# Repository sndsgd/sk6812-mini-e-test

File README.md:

# `sk6812-mini-e-test`

I've successfully used SK6812-MINI-E LEDs in several projects recently, and I'm considering using _lots_ of them in the near future. I'll be using this little board to verify performance and power requirements before scaling to thousands of LEDs.

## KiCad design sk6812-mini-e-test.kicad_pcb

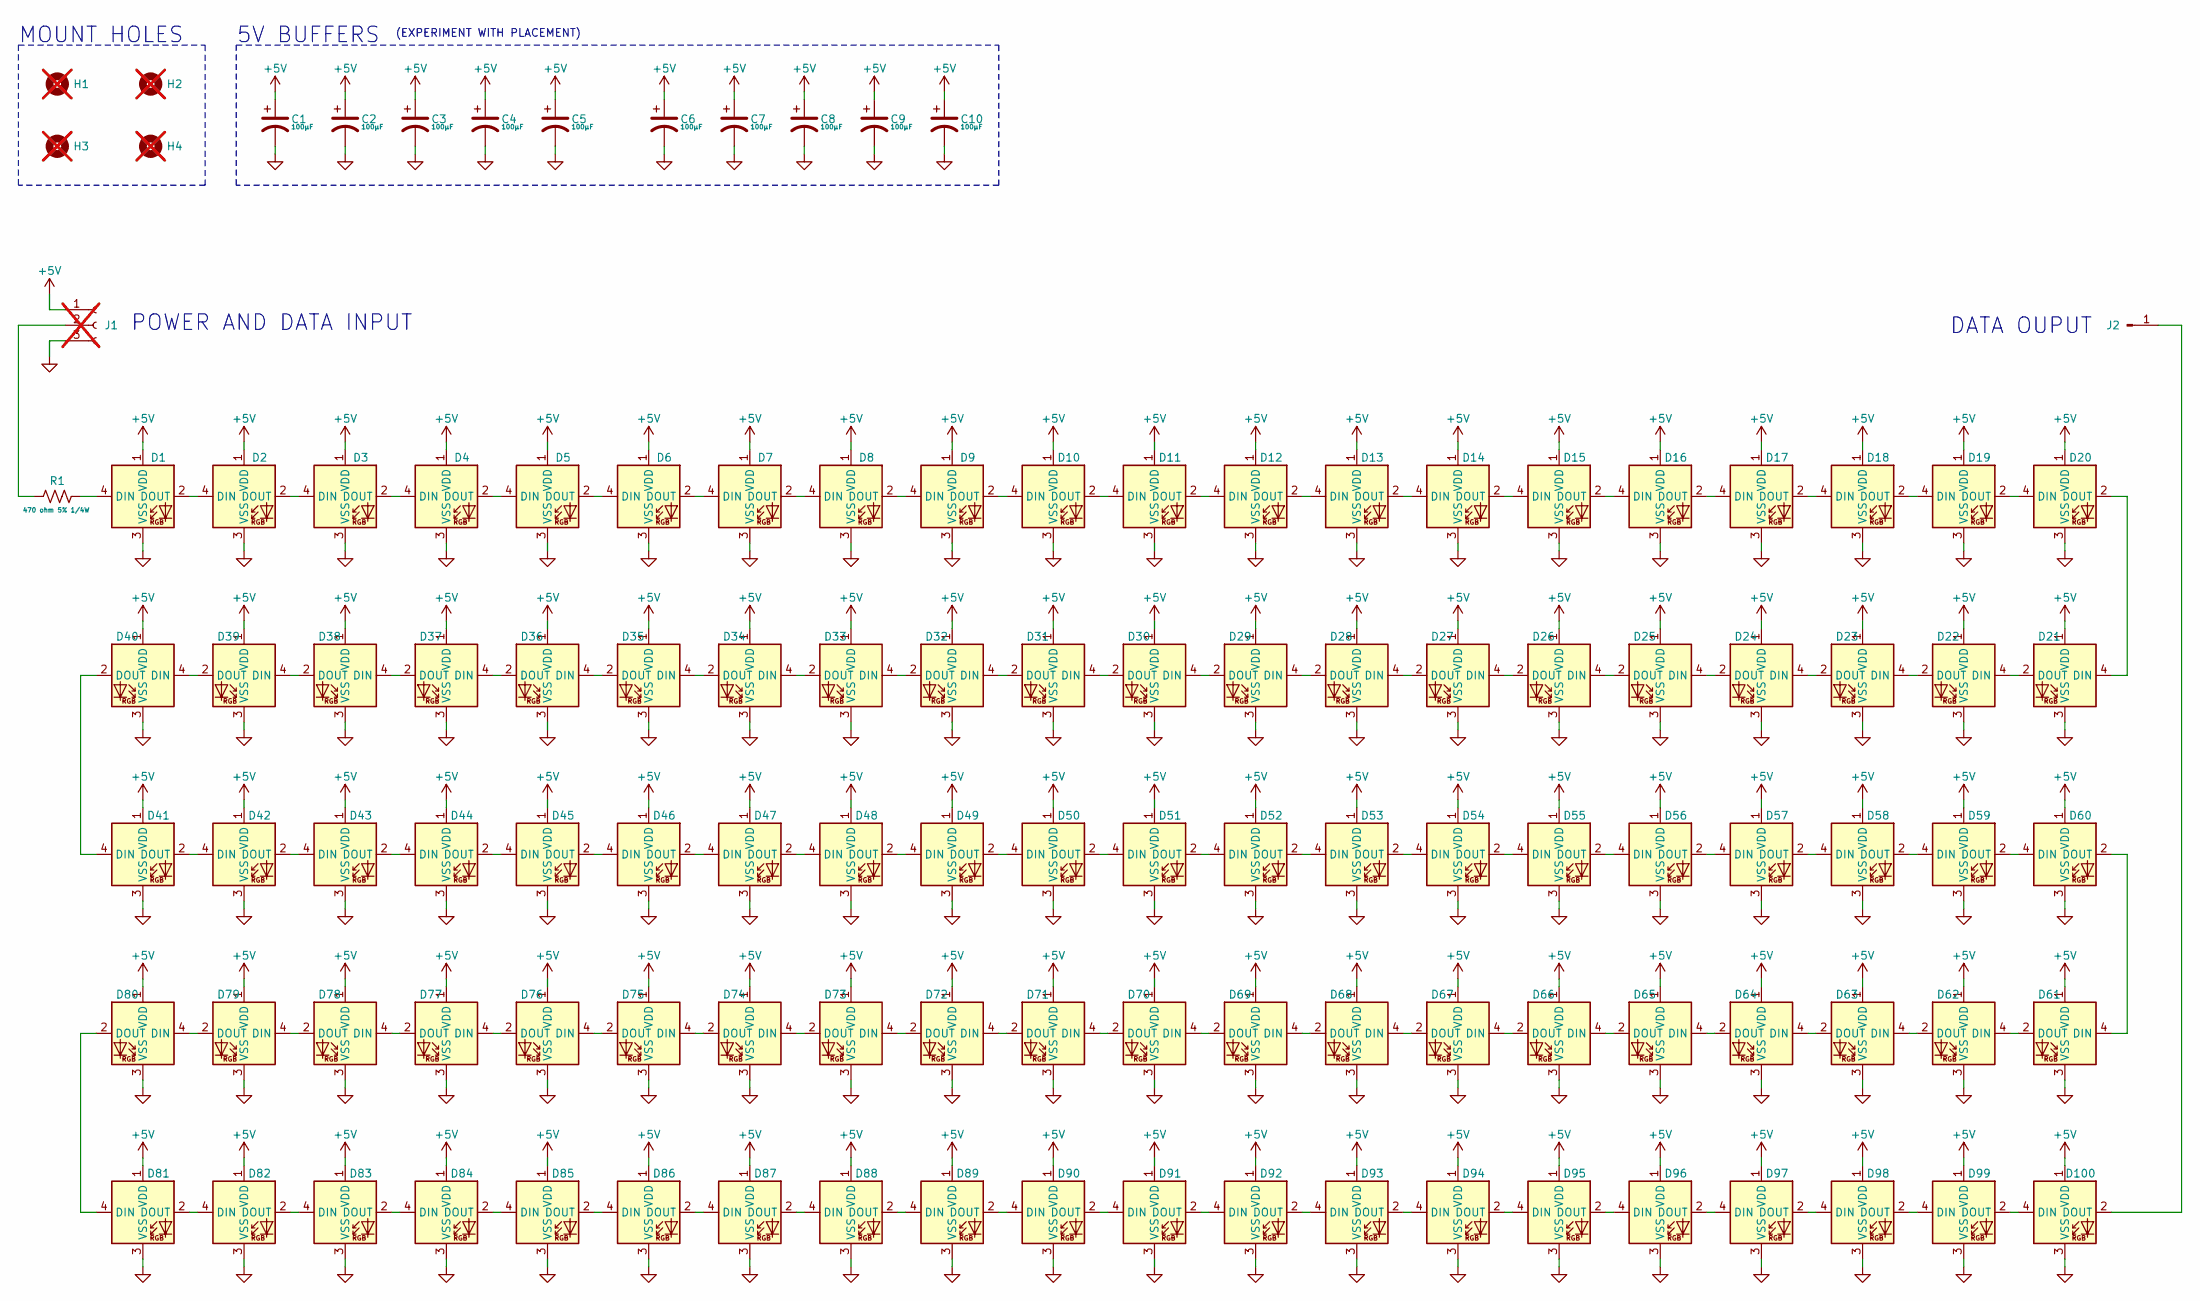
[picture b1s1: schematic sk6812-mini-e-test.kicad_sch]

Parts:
C1, C2, C3, C4, C5, C6, C7, C8, C9, C10: 100µF; C_1210_3225Metric; MPN GRM32ER61A107ME20L; LCSC C84455
D1, D2, D3, D4, D5, D6, D7, D8, D9, D10, D11, D12, D13, D14, D15, D16, D17, D18, D19, D20, D21, D22, D23, D24, D25, D26, D27, D28, D29, D30, D31, D32, D33, D34, D35, D36, D37, D38, D39, D40, D41, D42, D43, D44, D45, D46, D47, D48, D49, D50, D51, D52, D53, D54, D55, D56, D57, D58, D59, D60, D61, D62, D63, D64, D65, D66, D67, D68, D69, D70, D71, D72, D73, D74, D75, D76, D77, D78, D79, D80, D81, D82, D83, D84, D85, D86, D87, D88, D89, D90, D91, D92, D93, D94, D95, D96, D97, D98, D99, D100: SK6812-MINI-E; SK6812-MINI-E-BACK; MPN 4960; LCSC C5149201
H1, H2, H3, H4: INT; MountingHole_2.7mm_Pad_TopBottom; not fitted
J1: Conn_01x03_Socket; PinHeader_1x03_P2.54mm_Vertical; not fitted
J2: Conn_01x01_Pin; PinHeader_1x01_P2.54mm_Vertical
R1: 470 ohm 5% 1/4W; R_0805_2012Metric; MPN ERJ-T06J471V; LCSC C159918

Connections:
+5V: C1.1, C2.1, C3.1, C4.1, C5.1, C6.1, C7.1, C8.1, C9.1, C10.1, D1.1 (VDD), D2.1 (VDD), D3.1 (VDD), D4.1 (VDD), D5.1 (VDD), D6.1 (VDD), D7.1 (VDD), D8.1 (VDD), D9.1 (VDD), D10.1 (VDD), D11.1 (VDD), D12.1 (VDD), D13.1 (VDD), D14.1 (VDD), D15.1 (VDD), D16.1 (VDD), D17.1 (VDD), D18.1 (VDD), D19.1 (VDD), D20.1 (VDD), D21.1 (VDD), D22.1 (VDD), D23.1 (VDD), D24.1 (VDD), D25.1 (VDD), D26.1 (VDD), D27.1 (VDD), D28.1 (VDD), D29.1 (VDD), D30.1 (VDD), D31.1 (VDD), D32.1 (VDD), D33.1 (VDD), D34.1 (VDD), D35.1 (VDD), D36.1 (VDD), D37.1 (VDD), D38.1 (VDD), D39.1 (VDD), D40.1 (VDD), D41.1 (VDD), D42.1 (VDD), D43.1 (VDD), D44.1 (VDD), D45.1 (VDD), D46.1 (VDD), D47.1 (VDD), D48.1 (VDD), D49.1 (VDD), D50.1 (VDD), D51.1 (VDD), D52.1 (VDD), D53.1 (VDD), D54.1 (VDD), D55.1 (VDD), D56.1 (VDD), D57.1 (VDD), D58.1 (VDD), D59.1 (VDD), D60.1 (VDD), D61.1 (VDD), D62.1 (VDD), D63.1 (VDD), D64.1 (VDD), D65.1 (VDD), D66.1 (VDD), D67.1 (VDD), D68.1 (VDD), D69.1 (VDD), D70.1 (VDD), D71.1 (VDD), D72.1 (VDD), D73.1 (VDD), D74.1 (VDD), D75.1 (VDD), D76.1 (VDD), D77.1 (VDD), D78.1 (VDD), D79.1 (VDD), D80.1 (VDD), D81.1 (VDD), D82.1 (VDD), D83.1 (VDD), D84.1 (VDD), D85.1 (VDD), D86.1 (VDD), D87.1 (VDD), D88.1 (VDD), D89.1 (VDD), D90.1 (VDD), D91.1 (VDD), D92.1 (VDD), D93.1 (VDD), D94.1 (VDD), D95.1 (VDD), D96.1 (VDD), D97.1 (VDD), D98.1 (VDD), D99.1 (VDD), D100.1 (VDD), J1.1
GND: C1.2, C2.2, C3.2, C4.2, C5.2, C6.2, C7.2, C8.2, C9.2, C10.2, D1.3 (VSS), D2.3 (VSS), D3.3 (VSS), D4.3 (VSS), D5.3 (VSS), D6.3 (VSS), D7.3 (VSS), D8.3 (VSS), D9.3 (VSS), D10.3 (VSS), D11.3 (VSS), D12.3 (VSS), D13.3 (VSS), D14.3 (VSS), D15.3 (VSS), D16.3 (VSS), D17.3 (VSS), D18.3 (VSS), D19.3 (VSS), D20.3 (VSS), D21.3 (VSS), D22.3 (VSS), D23.3 (VSS), D24.3 (VSS), D25.3 (VSS), D26.3 (VSS), D27.3 (VSS), D28.3 (VSS), D29.3 (VSS), D30.3 (VSS), D31.3 (VSS), D32.3 (VSS), D33.3 (VSS), D34.3 (VSS), D35.3 (VSS), D36.3 (VSS), D37.3 (VSS), D38.3 (VSS), D39.3 (VSS), D40.3 (VSS), D41.3 (VSS), D42.3 (VSS), D43.3 (VSS), D44.3 (VSS), D45.3 (VSS), D46.3 (VSS), D47.3 (VSS), D48.3 (VSS), D49.3 (VSS), D50.3 (VSS), D51.3 (VSS), D52.3 (VSS), D53.3 (VSS), D54.3 (VSS), D55.3 (VSS), D56.3 (VSS), D57.3 (VSS), D58.3 (VSS), D59.3 (VSS), D60.3 (VSS), D61.3 (VSS), D62.3 (VSS), D63.3 (VSS), D64.3 (VSS), D65.3 (VSS), D66.3 (VSS), D67.3 (VSS), D68.3 (VSS), D69.3 (VSS), D70.3 (VSS), D71.3 (VSS), D72.3 (VSS), D73.3 (VSS), D74.3 (VSS), D75.3 (VSS), D76.3 (VSS), D77.3 (VSS), D78.3 (VSS), D79.3 (VSS), D80.3 (VSS), D81.3 (VSS), D82.3 (VSS), D83.3 (VSS), D84.3 (VSS), D85.3 (VSS), D86.3 (VSS), D87.3 (VSS), D88.3 (VSS), D89.3 (VSS), D90.3 (VSS), D91.3 (VSS), D92.3 (VSS), D93.3 (VSS), D94.3 (VSS), D95.3 (VSS), D96.3 (VSS), D97.3 (VSS), D98.3 (VSS), D99.3 (VSS), D100.3 (VSS), J1.3
unnamed: D1.4 (DIN), R1.2
unnamed: D1.2 (DOUT), D2.4 (DIN)
unnamed: D2.2 (DOUT), D3.4 (DIN)
unnamed: D3.2 (DOUT), D4.4 (DIN)
unnamed: D4.2 (DOUT), D5.4 (DIN)
unnamed: D5.2 (DOUT), D6.4 (DIN)
unnamed: D6.2 (DOUT), D7.4 (DIN)
unnamed: D7.2 (DOUT), D8.4 (DIN)
unnamed: D8.2 (DOUT), D9.4 (DIN)
unnamed: D9.2 (DOUT), D10.4 (DIN)
unnamed: D10.2 (DOUT), D11.4 (DIN)
unnamed: D11.2 (DOUT), D12.4 (DIN)
unnamed: D12.2 (DOUT), D13.4 (DIN)
unnamed: D13.2 (DOUT), D14.4 (DIN)
unnamed: D14.2 (DOUT), D15.4 (DIN)
unnamed: D15.2 (DOUT), D16.4 (DIN)
unnamed: D16.2 (DOUT), D17.4 (DIN)
unnamed: D17.2 (DOUT), D18.4 (DIN)
unnamed: D18.2 (DOUT), D19.4 (DIN)
unnamed: D19.2 (DOUT), D20.4 (DIN)
unnamed: D20.2 (DOUT), D21.4 (DIN)
unnamed: D21.2 (DOUT), D22.4 (DIN)
unnamed: D22.2 (DOUT), D23.4 (DIN)
unnamed: D23.2 (DOUT), D24.4 (DIN)
unnamed: D24.2 (DOUT), D25.4 (DIN)
unnamed: D25.2 (DOUT), D26.4 (DIN)
unnamed: D26.2 (DOUT), D27.4 (DIN)
unnamed: D27.2 (DOUT), D28.4 (DIN)
unnamed: D28.2 (DOUT), D29.4 (DIN)
unnamed: D29.2 (DOUT), D30.4 (DIN)
unnamed: D30.2 (DOUT), D31.4 (DIN)
unnamed: D31.2 (DOUT), D32.4 (DIN)
unnamed: D32.2 (DOUT), D33.4 (DIN)
unnamed: D33.2 (DOUT), D34.4 (DIN)
unnamed: D34.2 (DOUT), D35.4 (DIN)
unnamed: D35.2 (DOUT), D36.4 (DIN)
unnamed: D36.2 (DOUT), D37.4 (DIN)
unnamed: D37.2 (DOUT), D38.4 (DIN)
unnamed: D38.2 (DOUT), D39.4 (DIN)
unnamed: D39.2 (DOUT), D40.4 (DIN)
unnamed: D40.2 (DOUT), D41.4 (DIN)
unnamed: D41.2 (DOUT), D42.4 (DIN)
unnamed: D42.2 (DOUT), D43.4 (DIN)
unnamed: D43.2 (DOUT), D44.4 (DIN)
unnamed: D44.2 (DOUT), D45.4 (DIN)
unnamed: D45.2 (DOUT), D46.4 (DIN)
unnamed: D46.2 (DOUT), D47.4 (DIN)
unnamed: D47.2 (DOUT), D48.4 (DIN)
unnamed: D48.2 (DOUT), D49.4 (DIN)
unnamed: D49.2 (DOUT), D50.4 (DIN)
unnamed: D50.2 (DOUT), D51.4 (DIN)
unnamed: D51.2 (DOUT), D52.4 (DIN)
unnamed: D52.2 (DOUT), D53.4 (DIN)
unnamed: D53.2 (DOUT), D54.4 (DIN)
unnamed: D54.2 (DOUT), D55.4 (DIN)
unnamed: D55.2 (DOUT), D56.4 (DIN)
unnamed: D56.2 (DOUT), D57.4 (DIN)
unnamed: D57.2 (DOUT), D58.4 (DIN)
unnamed: D58.2 (DOUT), D59.4 (DIN)
unnamed: D59.2 (DOUT), D60.4 (DIN)
unnamed: D60.2 (DOUT), D61.4 (DIN)
unnamed: D61.2 (DOUT), D62.4 (DIN)
unnamed: D62.2 (DOUT), D63.4 (DIN)
unnamed: D63.2 (DOUT), D64.4 (DIN)
unnamed: D64.2 (DOUT), D65.4 (DIN)
unnamed: D65.2 (DOUT), D66.4 (DIN)
unnamed: D66.2 (DOUT), D67.4 (DIN)
unnamed: D67.2 (DOUT), D68.4 (DIN)
unnamed: D68.2 (DOUT), D69.4 (DIN)
unnamed: D69.2 (DOUT), D70.4 (DIN)
unnamed: D70.2 (DOUT), D71.4 (DIN)
unnamed: D71.2 (DOUT), D72.4 (DIN)
unnamed: D72.2 (DOUT), D73.4 (DIN)
unnamed: D73.2 (DOUT), D74.4 (DIN)
unnamed: D74.2 (DOUT), D75.4 (DIN)
unnamed: D75.2 (DOUT), D76.4 (DIN)
unnamed: D76.2 (DOUT), D77.4 (DIN)
unnamed: D77.2 (DOUT), D78.4 (DIN)
unnamed: D78.2 (DOUT), D79.4 (DIN)
unnamed: D79.2 (DOUT), D80.4 (DIN)
unnamed: D80.2 (DOUT), D81.4 (DIN)
unnamed: D81.2 (DOUT), D82.4 (DIN)
unnamed: D82.2 (DOUT), D83.4 (DIN)
unnamed: D83.2 (DOUT), D84.4 (DIN)
unnamed: D84.2 (DOUT), D85.4 (DIN)
unnamed: D85.2 (DOUT), D86.4 (DIN)
unnamed: D86.2 (DOUT), D87.4 (DIN)
unnamed: D87.2 (DOUT), D88.4 (DIN)
unnamed: D88.2 (DOUT), D89.4 (DIN)
unnamed: D89.2 (DOUT), D90.4 (DIN)
unnamed: D90.2 (DOUT), D91.4 (DIN)
unnamed: D91.2 (DOUT), D92.4 (DIN)
unnamed: D92.2 (DOUT), D93.4 (DIN)
unnamed: D93.2 (DOUT), D94.4 (DIN)
unnamed: D94.2 (DOUT), D95.4 (DIN)
unnamed: D95.2 (DOUT), D96.4 (DIN)
unnamed: D96.2 (DOUT), D97.4 (DIN)
unnamed: D97.2 (DOUT), D98.4 (DIN)
unnamed: D98.2 (DOUT), D99.4 (DIN)
unnamed: D99.2 (DOUT), D100.4 (DIN)
unnamed: D100.2 (DOUT), J2.1
unnamed: J1.2, R1.1

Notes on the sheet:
DATA OUPUT
POWER AND DATA INPUT
(EXPERIMENT WITH PLACEMENT)
MOUNT HOLES
5V BUFFERS

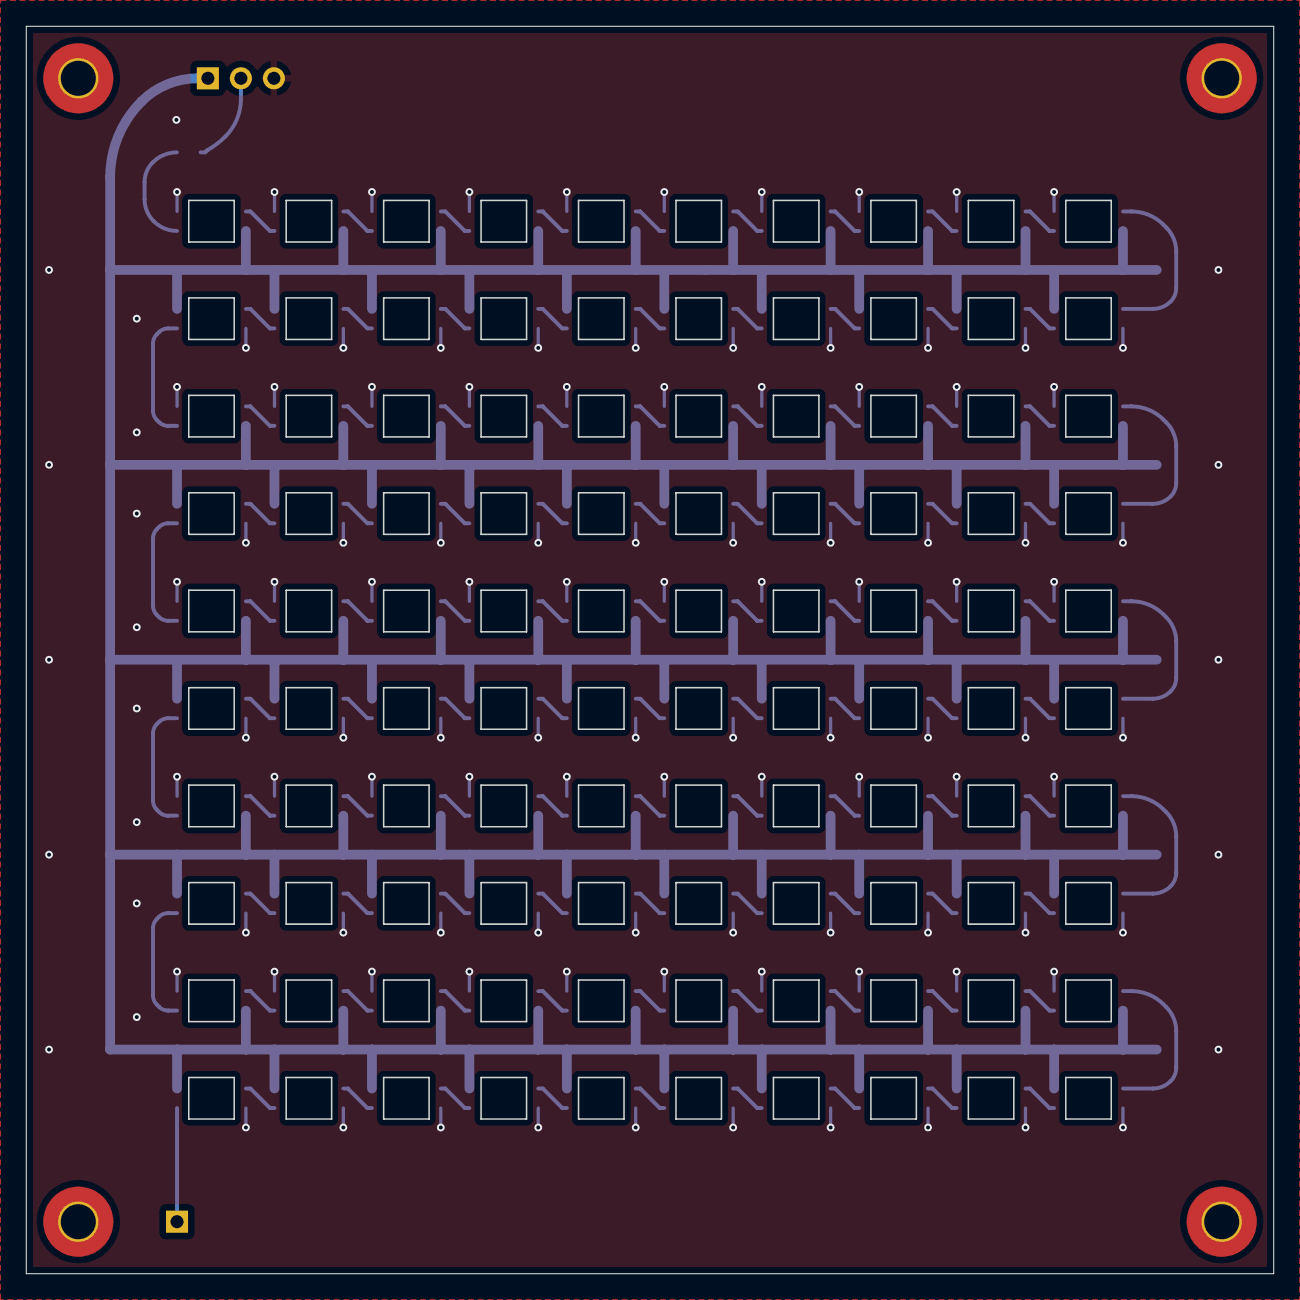
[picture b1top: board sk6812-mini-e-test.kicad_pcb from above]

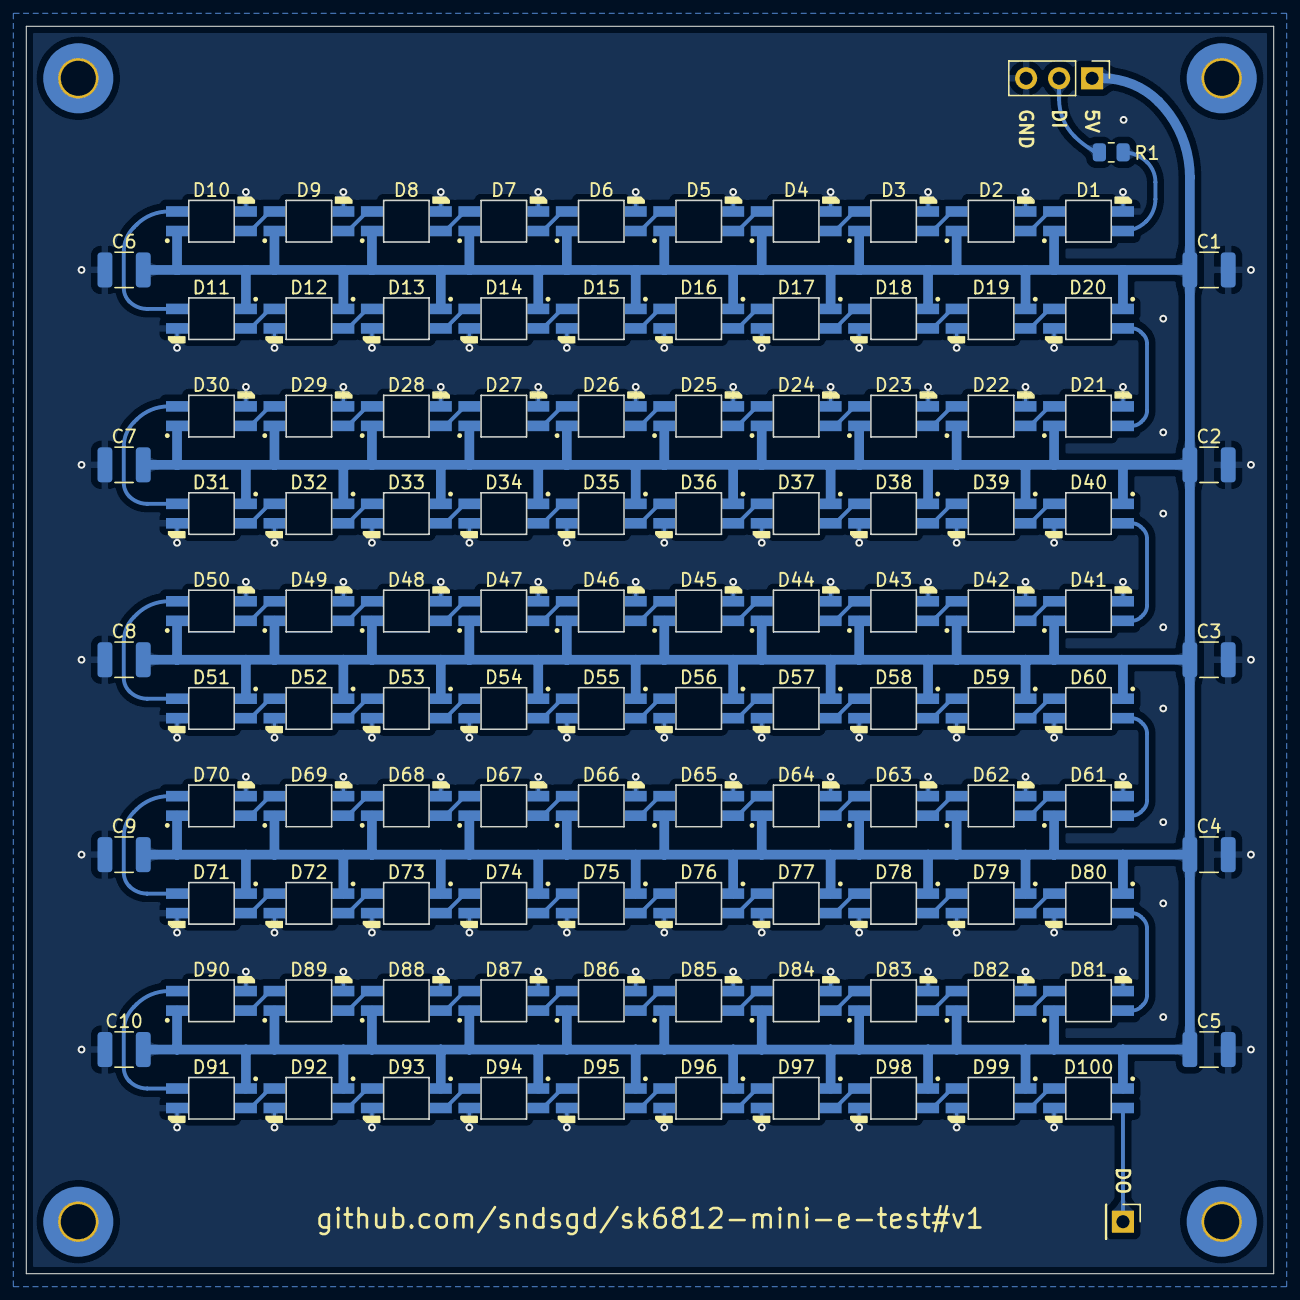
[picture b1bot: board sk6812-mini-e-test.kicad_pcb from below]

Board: 2 copper layers, 96.0 x 96.0 mm, 117 parts (13 on the bottom side), 104 nets.

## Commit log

2024-08-23 add license
